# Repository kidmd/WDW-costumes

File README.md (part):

# Main Street Electrical Parade - Synchronized LED Costumes (WDW 10K)

This project powers synchronized, addressable LED lighting across **7 runner costumes** inspired by Disney's **Main Street Electrical Parade** for the Walt Disney World 10K.

Worn by our **7-member family running team** (2 brothers, 1 sister, 1 brother-in-law, and 3 sisters-in-law) and engineered with love by the **3 brothers** (2 running, 1 supporting behind the scenes).

---

## The Concept

Each runner wears a matte black technical running shirt outlined with glow-in-the-dark paint and illuminated by individually addressable **WS2812B "Seed" / Pebble LEDs** to replicate the vintage incandescent bulbs of the parade floats.

An **ESP32** microcontroller on each runner coordinates lighting patterns wirelessly in real time using **ESP-NOW** (connectionless peer-to-peer 2.4 GHz radio), requiring **no Wi-Fi router or cellular service**.

### The 7 Floats Roster

1. **The Train (Casey Jr.):** Warm white chugging locomotive headlight & steam pulses (parade leader pulling the Title Drum).
2. **The Title Drum:** Golden chasing marquee border, "Disney" electric text accent.
3. **The Turtle:** Whimsical spinning shell spirals, blinking amber eyes, and teal/green shell pattern.
4. **The Snail:** Multi-color rotating rainbow spiral shell wheels and neon antennae glow.
5. **The Pirate Ship:** Billowing crimson sails, antique gold masts & decks, and emerald ocean waves.
6. **Pete's Dragon (Elliott):** Chartreuse/green body scales with orange/red fire breathing effect.
7. **To Honor America (Flag & Eagle):** Patriotic red, white, and blue finale fireworks shimmer with majestic illuminated eagle.

---

## Hardware Specifications

* **Microcontrollers:** ESP32 (e.g. ESP32-WROOM-32D or Seeed XIAO ESP32)
* **LED Strands:** 200 WS2812B / WS2811 Addressable 5V Seed/Pebble Pixels (100 front + 100 back duplicated, black wire, ~1" to 2" spacing)
* **Data Resistor:** 220 Ω to 470 Ω inline on the data line between GPIO 16 and LED Data-In
* **Power Source:** 5V USB portable power bank (5,000–20,000 mAh rating, FastLED hardware limited to 2000 mA / 2.0A) per runner with built-in simulator Battery Life & Power Budget Calculator
* **Costume Simulation:** Visual browser-based layout engine (`python simulator.py` @ `localhost:8000`) with built-in presets (Pete's Dragon, The Pirate Ship, Casey Jr., Title Drum, Turtle, Snail, Eagle), multi-layer Cricut Heat Transfer Vinyl (HTV) cut file exporter suite (All-in-One master SVG, color-mat-by-color-mat SVGs, and 6×3mm tangent pill cutouts with 4-corner heat press registration marks), Universal Undo / Redo engine (`Ctrl+Z` / `Ctrl+Y`) with 50-step snapshot history and floating toolbar buttons, 7-Shirt Fleet Show Creator Studio featuring a 19-block choreography palette (traveling waves, dual collision shockwaves, butterfly ripples, fairy dust waterfalls, fleet pulses, wig-wags, sparkle storms, baton chases, and grand finales), interactive NLE-grade visual timeline block editor (drag-to-stretch, rolling trim, and drag-and-drop reordering), Animation Group Spatial Suite & Pre-Built Shape Stamp Library (parametric Circles/Wheels, Arches, Waves, Stars/Sparkles, Lines/Rulers, and Fireworks Starbursts with aspect-ratio correction, interactive click-to-place positioning, Cross-Shirt Clipboard, Rotate 90°, Flip H/V, Scale LED Spacing while maintaining exact shape, and auto-rearranging remaining unassigned LEDs), multi-float live Wi-Fi UDP streaming (`Opcode 0x02`), pre-race Corral Roll Call & ESP-NOW Fleet Radar (instant identification strobe, 4s rapid attendance wave, signal RSSI, battery voltage, and lineup readiness), race-day battery life calculator with 7-float power breakdown, double-tap 4-second rapid attendance wave, 300ms debounced one-shot trigger and early stop, "Snap to 30.0s" sequence normalization, JSON show persistence, 1-click & double-click Single View editing from fleet cards, real 700-LED mini-shirt visualizer, multi-mode wireless sync (ESP-NOW Wave, Free-Run, Show Sequence), full-graphic LED re-distribution (maintaining strictly 100 LEDs per shirt), and authentic runDisney 10K Race Bib (#1952) with Chip & Dale and BibBoards fastener clearance.
* **3D-Printable Flexible TPU Armor Plates & Protective Rear Lids (5-Color Multi-Material & Single STL):** High-speed parametric fabrication pipeline (`scripts/compile_clean_tpu_panel.py`) compiling wearable 9.0mm deep-chassis armor trays and matching **2.0mm protective rear cover lids** (`tpu_panel_{front|back}_lid.stl`). Features **5-Color Multi-Material FDM printing** (for Bambu Lab AMS / Snapmaker Dual) with a monolithic black structural chassis (`chassis_black.stl`), 4 zero-overlap jigsaw front color inlays, 3x3mm / Ø 3.4mm through-aperture windows for LEDs, and a **14-point M2 perimeter screw fastening system** (with dedicated extremity clamping at jaw, ears, tail tip, flank, and heel corners) with 1.2mm stepped alignment ridges. Includes 1-click **Bambu 3MF** and **5-Color ZIP bundles** (packaging tray, inlays, and rear lid), selectable plate sizing (Small ~6.5", Medium ~8.0", Large capped to $\le 245.0\text{ mm}$ for $256\times 256\text{ mm}$ build plates), selectable LED counts (50, 75, 100 LEDs), and an interactive 3D WebGL inspector (`#tpuPreviewModal` & `3d_panels/tpu_panel_preview.html`) with live Tray vs Rear Lid 3D inspection.
* **Universal 100mm × 100mm 6×6 LED Matrix Panels (Turnkey JLCPCB SMT & Felt Pocket):** Cost-optimized modular FR-4 PCB tile system. 4 identical 36-LED tiles cluster into a 144-LED chest array ($202\text{ mm} \times 202\text{ mm}$) featuring an authentic staggered brick layout with calibrated $17.0\text{ mm}$ pitch, making the 4-board cluster 100% optically seamless across the $2.0\text{ mm}$ felt living hinge gap. Available in two production variants:
  - **Front-Mounted Variant (`pcb/`):** 8 horizontal JST-PH 2.0mm ports set back $10.0\text{ mm}$ into inter-pixel valleys with diagonal $50\text{ mm}$ cable routing ($\le 5\text{ mm}$ height profile). Single-sided SMT using JLCPCB "Economic PCBA".
  - **Bottom-Mounted Variant (`pcb/bottom_connectors/`):** 100% flush front face (only 0.9mm LEDs and 0.5mm 0402 caps) for direct contact against fabric or 3D-printed faceplates with **0.0 mm gap and zero light bleed**. All 8 JST-PH headers are on the rear layer (`B.Cu`), featuring symmetrical **$22.0\text{ mm}$ straight-line spans** in all 4 directions for $50\text{ mm}$ pre-crimped JST cables. Requires JLCPCB double-sided "Standard PCBA" ($+\$0.80$ per board for a 75-board fleet order).
  - Both variants include 4× corner M3 screw holes, 4× dedicated fabric sewing eyelets, soldermask LED numbering (`1`..`36`), hidden component references for clean lenses, turnkey RS-274X Gerbers, JLCPCB BOM/CPL files, and interactive dual-view web inspectors (`universal_6x6_preview.html` and `universal_6x6_bottom_preview.html`).
* **Monolithic 200mm × 200mm LED Panels (Zero-Wire Single-Sided SMT Displays):** Large single-piece $200.0\text{ mm} \times 200.0\text{ mm}$ ($7.87'' \times 7.87''$) boards featuring 100% internal etched copper wiring (zero inter-tile jumper cables) and pure single-sided SMT assembly (LEDs and Caps on Top layer only, qualifying for JLCPCB **Economic PCBA** at $\sim \$15.00$ setup fee, saving $\$55.00$ per batch). Equipped with $2.54\text{ mm}$ pitch plated through-hole solder pins for IN and OUT (solderable from Front or Back) and dual S-curve wire strain-relief anchor holes. Available in two density options:
  - **144-LED Model (`pcb/monolithic_200mm_144/`):** 12×12 staggered brick matrix ($15.5\text{ mm} \times 16.0\text{ mm}$ pitch). Complete with RS-274X Gerbers, BOM, CPL, KiCad PCB, and interactive HTML preview. Fleet cost for 8 suits (18 boards): **$\approx \$220.72$ ($\$27.59$ per runner for Front + Back)**.
  - **288-LED Double-Density Model (`pcb/monolithic_200mm_288/`):** Exactly twice as many LEDs ($144 \times 2 = 288$ LEDs) in an 18×16 isotropic offset lattice ($11.6\text{ mm} \times 10.6\text{ mm}$ pitch). High-definition "Retina" resolution for intricate parade graphics. FastLED hardware power limited to 2.0A. Complete with RS-274X Gerbers, BOM, CPL, KiCad PCB, and interactive HTML preview. Fleet cost for 8 suits (18 boards): **$\approx \$368.45$ ($\$46.06$ per runner for Front + Back)**.
* **3D-Printable PLA PCB Test Mockups (`3d_panels/mockups/`):** Physics-calibrated physical test "mules" to evaluate chest curvature, thickness, weight, and bounce on a running shirt before ordering from JLCPCB. Using the **2.5mm Equivalence Rule**, printing at 100% solid infill matches both the real $2.5\text{ mm}$ board+LED envelope AND the exact weight (**$123.7\text{ grams}$ PLA vs. $126.5\text{ grams}$ real PCB — a 97.8% match!**). Includes `mockup_monolithic_200x200.stl`, `mockup_modular_100x100.stl`, and an interactive 3D WebGL preview (`mockups_preview.html`).
* **Pete's Dragon 200mm × 200mm Optical Backlighting Test Panels (`3d_panels/backlight_test/`):** Flat multi-color test panels designed to evaluate filament translucency and rear LED backlighting diffusion across 4 calibrated thicknesses (**1.00 mm, 0.80 mm, 0.60 mm, and 0.48 mm**). Features a pure flat $200.0\text{ mm} \times 200.0\text{ mm}$ black chassis (all LED holes, trenches, walls, eyelets, and screw holes removed), with Pete's Dragon ($180.0\text{ mm} \times 163.2\text{ mm}$) centered inside a $180\text{ mm}$ square. All artwork colors (Green, Magenta, Yellow, White) extend 100% through the full Z thickness for optical transmission. Includes native multi-material `.3mf` files (Bambu Studio / OrcaSlicer / Snapmaker Luban), individual color STLs, parametric OpenSCAD script, and an interactive 3D WebGL preview (`backlight_test_preview.html`).
* **BTF-LIGHTING 16×16 (256-Pixel) Flexible FPCB Matrix (Default Standard Architecture):** The primary costume standard across the simulator and firmware. Features a commercial $160.0\text{ mm} \times 160.0\text{ mm}$ ($10.0\text{ mm}$ pitch) WS2812B ECO 256-LED flexible matrix mounted behind a **$176.0\text{ mm} \times 176.0\text{ mm}$ flat square 3D-printed plate** ($2.0\text{ mm}$ perimeter frame, full $2.0\text{ mm}$ pocket depth with strictly $0.0\text{ mm}$ lip, soft 6.0mm anti-snag rounded corners, and 4 corner $\varnothing 2.8\text{ mm}$ shirt-stitching holes). Evenly distributes **~50 Windowed LEDs** ($5.4\text{ mm} \times 5.4\text{ mm}$ through-hole apertures) and **~25 Backlighting LEDs** (diffused subsurface glow through thin colored PLA/TPU at 50% brightness) via Farthest-Point Sampling while keeping the remaining **~181 LEDs Dark** (~1.35A max draw @ 5V). Features a **$0.40\text{ mm}$ Clear Diffuser Backing Layer** default (spanning the full $160.4 \times 160.4\text{ mm}$ cavity flush to the 2mm frame), default **$0.60\text{ mm}$ Front Graphic Faceplate** ($1.00\text{ mm}$ total panel thickness), **$2.00\text{ mm}$ Perimeter Frame Depth**, face-down print orientation on PEI bed, automatic slicer pause at $Z = 0.60\text{ mm}$ (Layer 4) for swapping Nozzle 3 / Toolhead 3 on the Snapmaker U1 to Clear filament, and native multi-material `.3mf` project with embedded extruder mapping. Governed by a **Global Hardware Architecture Switcher** (`[ 🔲 16×16 Matrix (Default) ]` | `[ 🧵 Fairy Lights (Legacy) ]`) in the top navigation bar, decluttering the Layout and Deploy tabs (top-header **📁 Upload Artwork** modal, legacy-scoped placement guides, fixed 57% height/100% scale race bib, and Groups-tab-dedicated inspector) while preserving 100% backward compatibility for legacy prototype fairy light rigs.

---

## Wireless Synchronization (ESP-NOW)

* **Protocol:** ESP-NOW broadcast (Destination MAC `FF:FF:FF:FF:FF:FF`).
* **Architecture:**
  * **Float 1 (Primary Master Leader):** Front locomotive broadcasting timing ticks, BPM tempo, master brightness, show triggers, and photo mode.
  * **Float 7 (Co-Leader / Rear Marshal):** Rear anchor with full co-leader authority to command the rear pack independently if runners split.
  * **Floats 2–6 (Followers):** Listen to broadcast packets, lock to master clock, and execute individual autonomous sequences or synchronized routines.
* **Dual Hardware Button Controls (Button 1: GPIO 4 / BOOT GPIO 0, Button 2: GPIO 33):**
  * **Power-Up (Plug USB):** Boots directly into **🌙 Corral Standby Mode** (12% dim midnight starlight twinkle, < 120mA), saving 80%+ battery during the 60–90 min starting wait.
  * **Button 1 — Single Tap (< 600ms):**
    * 👑 *Leader (Float 1 & 7):* When asleep or in Photo Mode, wakes **ENTIRE FLEET** into **Solo Show Mode** (individual float identities). When running awake, launches the **30s Synchronized Fleet Routine** (or toggles/cancels during active routine).
    * 👥 *Follower (Floats 2–6):* When asleep or in Photo Mode, wakes/exits **THAT RUNNER ONLY** into Solo Show Mode. When running awake, **IGNORED** (keeps parade show running without accidental interruption).
  * **Button 1 — Double Tap (< 400ms):**
    * 👑 *Leader:* Triggers **⚡ 4-Second Rapid Attendance Roll Call** wave across all 7 costumes.
    * 👥 *Follower:* Ignored (roll call reserved for Leader).
  * **Button 1 — Long Hold (5s):**
    * Enter **Float ID Configuration Mode** (1 to 7) with a 1s–4s progressive white LED charging meter and permanent NVS flash auto-save. Releasing before 5s cleanly aborts back to baseline without triggering show routines.
  * **Button 2 — Single Tap (< 600ms):**
    * 👑 *Leader:* Toggles **📸 Castle Photo Mode** (solid, steady, non-flickering full graphic background colors) across the **ENTIRE FLEET**.
    * 👥 *Follower:* Toggles **📸 Castle Photo Mode** **LOCALLY** (solid full graphic background colors) for that runner.
  * **Button 2 — Double Tap (< 400ms):**
    * 👑 *Leader:* Toggles **✨ 3% Warm White Starlight Mode** (~2500K golden incandescent filament glow with pure diamond sparkles) across the **ENTIRE FLEET** (with 2-pulse warm white confirmation). Tap or double-tap again resumes parade show.
    * 👥 *Follower:* Toggles **✨ 3% Warm White Starlight Mode** **LOCALLY** for that runner.
  * **Button 2 — Long Hold (3s):**
    * 👑 *Leader:* Drops **ENTIRE FLEET into Corral Standby (Sleep) Mode**. Stays locked in Standby even if held >3s—requiring an explicit click to enter Photo Mode.
    * 👥 *Follower:* Drops **THAT RUNNER ONLY into Corral Standby Mode**. Stays locked in Standby even if held >3s—waiting for physical release so it never accidentally pops into Photo Mode.

---

## ⚡ Quick Start for Family Runners & Crew (No Git Required!)

You don't need Git, Google Antigravity, or any programming tools:
1. **Download:** Click the green **`<> Code`** button above ➔ **`Download ZIP`** (or [Click Here to Download ZIP](https://github.com/kidmd/WDW-costumes/archive/refs/heads/main.zip)).
2. **Extract:** Right-click the `.zip` file and select **Extract All...** to any folder on your computer.
3. **Plug in & Flash:** Connect your ESP32 via USB and double-click **`flash_firmware.bat`** (Windows) or **`flash_firmware.command`** (Mac).
4. See **[`FLASHING_INSTRUCTIONS.md`](FLASHING_INSTRUCTIONS.md)** for complete hardware wiring and float selection instructions.

---

## Project Structure & Documentation

* [`ESP32_WIRING_PLAN.md`](ESP32_WIRING_PLAN.md): **🔌 ESP32 Hardware Wiring Plan & Electrical Specification** — Complete schematics, pinout tables, tactile button wiring, 4-pin orientation guide, 220–470 Ω data resistor, power bus injection, and computer power isolation rules.
* [`RACE_DAY_BUTTON_GUIDE.md`](RACE_DAY_BUTTON_GUIDE.md): **🏃🏰 Race Day Button Field Guide & Controller Cheat Sheet** — Pocket manual with gesture timings, Leader vs Follower matrices, chronological corral countdown playbook, and state flow diagrams.
* [`RACE_DAY_PACKING_CHECKLIST.md`](RACE_DAY_PACKING_CHECKLIST.md): **🏰 Race Day Packing Checklist & Field Manual** — Pre-race hardware checklist, spare ESP32s, battery survival, repair toolkit, weather kit, and countdown timeline for the 7-runner family team.
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
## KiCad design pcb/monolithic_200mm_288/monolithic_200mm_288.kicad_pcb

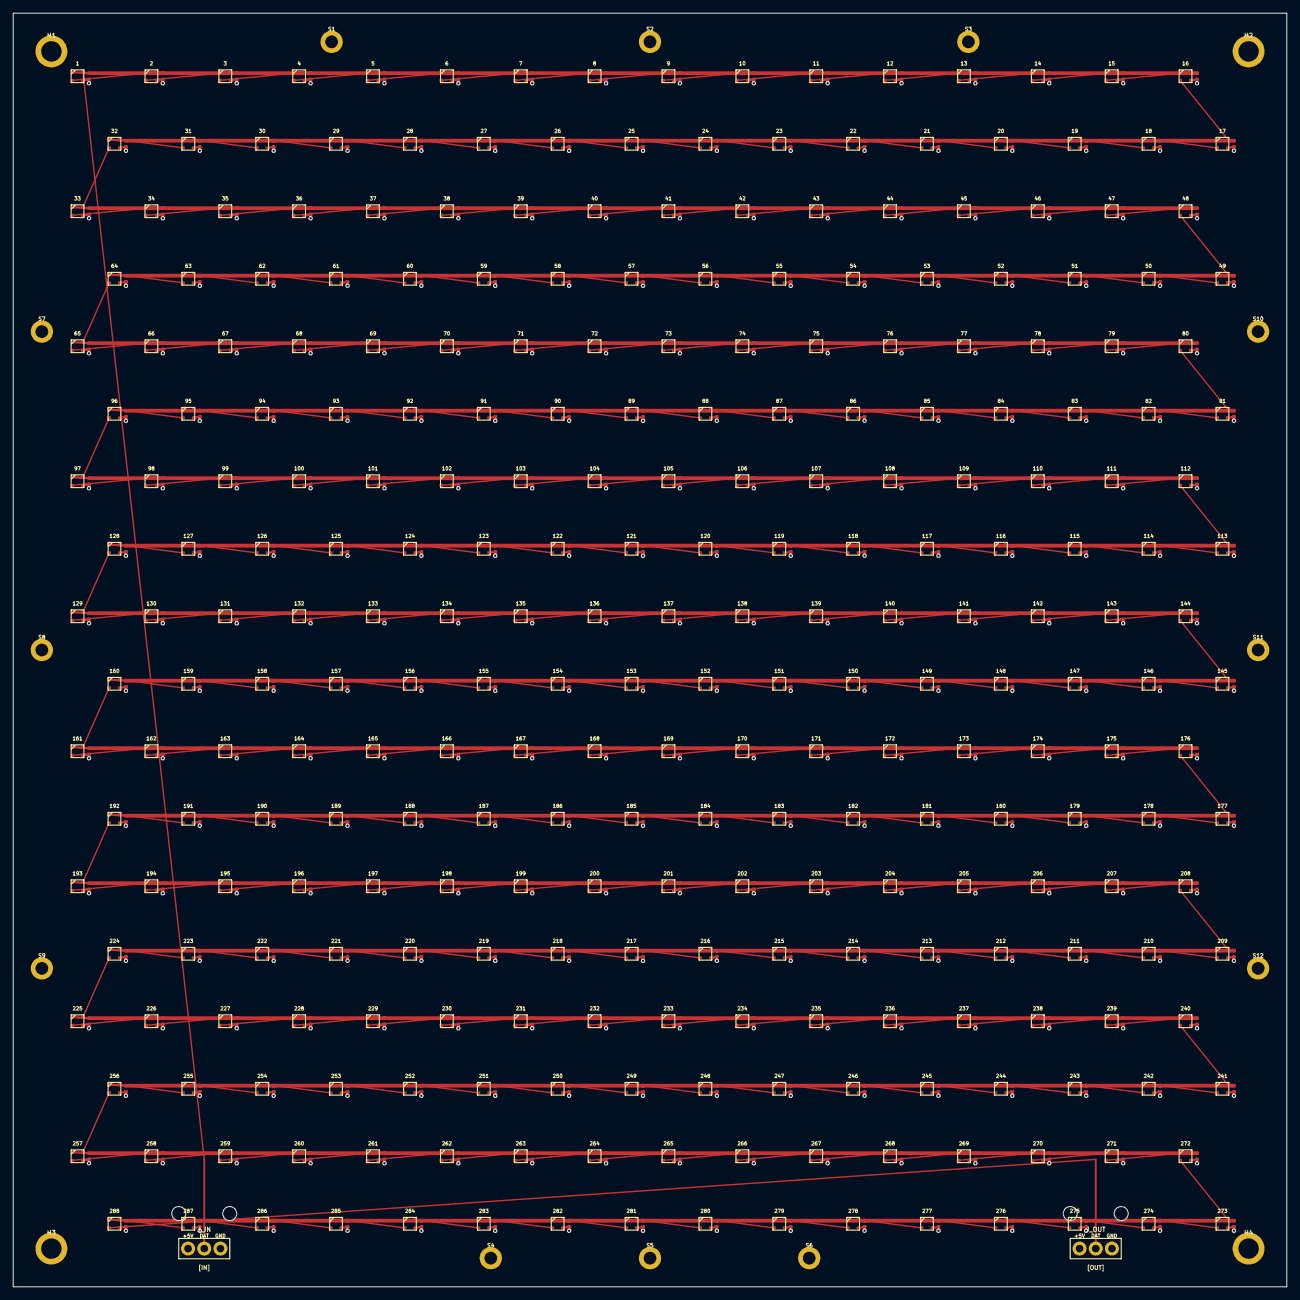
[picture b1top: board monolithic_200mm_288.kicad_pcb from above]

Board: 2 copper layers, 200.0 x 200.0 mm, 594 parts (0 on the bottom side), 291 nets.

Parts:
C1, C2, C3, C4, C5, C6, C7, C8, C9, C10, C11, C12, C13, C14, C15, C16, C17, C18, C19, C20, C21, C22, C23, C24, C25, C26, C27, C28, C29, C30, C31, C32, C33, C34, C35, C36, C37, C38, C39, C40, C41, C42, C43, C44, C45, C46, C47, C48, C49, C50, C51, C52, C53, C54, C55, C56, C57, C58, C59, C60, C61, C62, C63, C64, C65, C66, C67, C68, C69, C70, C71, C72, C73, C74, C75, C76, C77, C78, C79, C80, C81, C82, C83, C84, C85, C86, C87, C88, C89, C90, C91, C92, C93, C94, C95, C96, C97, C98, C99, C100, C101, C102, C103, C104, C105, C106, C107, C108, C109, C110, C111, C112, C113, C114, C115, C116, C117, C118, C119, C120, C121, C122, C123, C124, C125, C126, C127, C128, C129, C130, C131, C132, C133, C134, C135, C136, C137, C138, C139, C140, C141, C142, C143, C144, C145, C146, C147, C148, C149, C150, C151, C152, C153, C154, C155, C156, C157, C158, C159, C160, C161, C162, C163, C164, C165, C166, C167, C168, C169, C170, C171, C172, C173, C174, C175, C176, C177, C178, C179, C180, C181, C182, C183, C184, C185, C186, C187, C188, C189, C190, C191, C192, C193, C194, C195, C196, C197, C198, C199, C200, C201, C202, C203, C204, C205, C206, C207, C208, C209, C210, C211, C212, C213, C214, C215, C216, C217, C218, C219, C220, C221, C222, C223, C224, C225, C226, C227, C228, C229, C230, C231, C232, C233, C234, C235, C236, C237, C238, C239, C240, C241, C242, C243, C244, C245, C246, C247, C248, C249, C250, C251, C252, C253, C254, C255, C256, C257, C258, C259, C260, C261, C262, C263, C264, C265, C266, C267, C268, C269, C270, C271, C272, C273, C274, C275, C276, C277, C278, C279, C280, C281, C282, C283, C284, C285, C286, C287, C288: C_0402_1005Metric
D1, D2, D3, D4, D5, D6, D7, D8, D9, D10, D11, D12, D13, D14, D15, D16, D17, D18, D19, D20, D21, D22, D23, D24, D25, D26, D27, D28, D29, D30, D31, D32, D33, D34, D35, D36, D37, D38, D39, D40, D41, D42, D43, D44, D45, D46, D47, D48, D49, D50, D51, D52, D53, D54, D55, D56, D57, D58, D59, D60, D61, D62, D63, D64, D65, D66, D67, D68, D69, D70, D71, D72, D73, D74, D75, D76, D77, D78, D79, D80, D81, D82, D83, D84, D85, D86, D87, D88, D89, D90, D91, D92, D93, D94, D95, D96, D97, D98, D99, D100, D101, D102, D103, D104, D105, D106, D107, D108, D109, D110, D111, D112, D113, D114, D115, D116, D117, D118, D119, D120, D121, D122, D123, D124, D125, D126, D127, D128, D129, D130, D131, D132, D133, D134, D135, D136, D137, D138, D139, D140, D141, D142, D143, D144, D145, D146, D147, D148, D149, D150, D151, D152, D153, D154, D155, D156, D157, D158, D159, D160, D161, D162, D163, D164, D165, D166, D167, D168, D169, D170, D171, D172, D173, D174, D175, D176, D177, D178, D179, D180, D181, D182, D183, D184, D185, D186, D187, D188, D189, D190, D191, D192, D193, D194, D195, D196, D197, D198, D199, D200, D201, D202, D203, D204, D205, D206, D207, D208, D209, D210, D211, D212, D213, D214, D215, D216, D217, D218, D219, D220, D221, D222, D223, D224, D225, D226, D227, D228, D229, D230, D231, D232, D233, D234, D235, D236, D237, D238, D239, D240, D241, D242, D243, D244, D245, D246, D247, D248, D249, D250, D251, D252, D253, D254, D255, D256, D257, D258, D259, D260, D261, D262, D263, D264, D265, D266, D267, D268, D269, D270, D271, D272, D273, D274, D275, D276, D277, D278, D279, D280, D281, D282, D283, D284, D285, D286, D287, D288: LED_WS2812B-2020_PLCC4_2.0x2.0mm
H1, H2, H3, H4: MountingHole_3.2mm_M3
J_IN: PinHeader_1x03_P2.54mm_Vertical
J_OUT: PinHeader_1x03_P2.54mm_Vertical
S1, S2, S3, S4, S5, S6, S7, S8, S9, S10, S11, S12: MountingHole_2.0mm

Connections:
+5V: C1.1, C2.1, C3.1, C4.1, C5.1, C6.1, C7.1, C8.1, C9.1, C10.1, C11.1, C12.1, C13.1, C14.1, C15.1, C16.1, C17.1, C18.1, C19.1, C20.1, C21.1, C22.1, C23.1, C24.1, C25.1, C26.1, C27.1, C28.1, C29.1, C30.1, C31.1, C32.1, C33.1, C34.1, C35.1, C36.1, C37.1, C38.1, C39.1, C40.1, C41.1, C42.1, C43.1, C44.1, C45.1, C46.1, C47.1, C48.1, C49.1, C50.1, C51.1, C52.1, C53.1, C54.1, C55.1, C56.1, C57.1, C58.1, C59.1, C60.1, C61.1, C62.1, C63.1, C64.1, C65.1, C66.1, C67.1, C68.1, C69.1, C70.1, C71.1, C72.1, C73.1, C74.1, C75.1, C76.1, C77.1, C78.1, C79.1, C80.1, C81.1, C82.1, C83.1, C84.1, C85.1, C86.1, C87.1, C88.1, C89.1, C90.1, C91.1, C92.1, C93.1, C94.1, C95.1, C96.1, C97.1, C98.1, C99.1, C100.1, C101.1, C102.1, C103.1, C104.1, C105.1, C106.1, C107.1, C108.1, C109.1, C110.1, C111.1, C112.1, C113.1, C114.1, C115.1, C116.1, C117.1, C118.1, C119.1, C120.1, C121.1, C122.1, C123.1, C124.1, C125.1, C126.1, C127.1, C128.1, C129.1, C130.1, C131.1, C132.1, C133.1, C134.1, C135.1, C136.1, C137.1, C138.1, C139.1, C140.1, C141.1, C142.1, C143.1, C144.1, C145.1, C146.1, C147.1, C148.1, C149.1, C150.1, C151.1, C152.1, C153.1, C154.1, C155.1, C156.1, C157.1, C158.1, C159.1, C160.1, C161.1, C162.1, C163.1, C164.1, C165.1, C166.1, C167.1, C168.1, C169.1, C170.1, C171.1, C172.1, C173.1, C174.1, C175.1, C176.1, C177.1, C178.1, C179.1, C180.1, C181.1, C182.1, C183.1, C184.1, C185.1, C186.1, C187.1, C188.1, C189.1, C190.1, C191.1, C192.1, C193.1, C194.1, C195.1, C196.1, C197.1, C198.1, C199.1, C200.1, C201.1, C202.1, C203.1, C204.1, C205.1, C206.1, C207.1, C208.1, C209.1, C210.1, C211.1, C212.1, C213.1, C214.1, C215.1, C216.1, C217.1, C218.1, C219.1, C220.1, C221.1, C222.1, C223.1, C224.1, C225.1, C226.1, C227.1, C228.1, C229.1, C230.1, C231.1, C232.1, C233.1, C234.1, C235.1, C236.1, C237.1, C238.1, C239.1, C240.1, C241.1, C242.1, C243.1, C244.1, C245.1, C246.1, C247.1, C248.1, C249.1, C250.1, C251.1, C252.1, C253.1, C254.1, C255.1, C256.1, C257.1, C258.1, C259.1, C260.1, C261.1, C262.1, C263.1, C264.1, C265.1, C266.1, C267.1, C268.1, C269.1, C270.1, C271.1, C272.1, C273.1, C274.1, C275.1, C276.1, C277.1, C278.1, C279.1, C280.1, C281.1, C282.1, C283.1, C284.1, C285.1, C286.1, C287.1, C288.1, D1.1, D2.1, D3.1, D4.1, D5.1, D6.1, D7.1, D8.1, D9.1, D10.1, D11.1, D12.1, D13.1, D14.1, D15.1, D16.1, D17.1, D18.1, D19.1, D20.1, D21.1, D22.1, D23.1, D24.1, D25.1, D26.1, D27.1, D28.1, D29.1, D30.1, D31.1, D32.1, D33.1, D34.1, D35.1, D36.1, D37.1, D38.1, D39.1, D40.1, D41.1, D42.1, D43.1, D44.1, D45.1, D46.1, D47.1, D48.1, D49.1, D50.1, D51.1, D52.1, D53.1, D54.1, D55.1, D56.1, D57.1, D58.1, D59.1, D60.1, D61.1, D62.1, D63.1, D64.1, D65.1, D66.1, D67.1, D68.1, D69.1, D70.1, D71.1, D72.1, D73.1, D74.1, D75.1, D76.1, D77.1, D78.1, D79.1, D80.1, D81.1, D82.1, D83.1, D84.1, D85.1, D86.1, D87.1, D88.1, D89.1, D90.1, D91.1, D92.1, D93.1, D94.1, D95.1, D96.1, D97.1, D98.1, D99.1, D100.1, D101.1, D102.1, D103.1, D104.1, D105.1, D106.1, D107.1, D108.1, D109.1, D110.1, D111.1, D112.1, D113.1, D114.1, D115.1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
DATA_1: D1.4, J_IN.2
DATA_2: D1.2, D2.4
DATA_3: D2.2, D3.4
DATA_4: D3.2, D4.4
DATA_5: D4.2, D5.4
DATA_6: D5.2, D6.4
DATA_7: D6.2, D7.4
DATA_8: D7.2, D8.4
DATA_9: D8.2, D9.4
DATA_10: D9.2, D10.4
DATA_11: D10.2, D11.4
DATA_12: D11.2, D12.4
DATA_13: D12.2, D13.4
DATA_14: D13.2, D14.4
DATA_15: D14.2, D15.4
DATA_16: D15.2, D16.4
DATA_17: D16.2, D17.4
DATA_18: D17.2, D18.4
DATA_19: D18.2, D19.4
DATA_20: D19.2, D20.4
DATA_21: D20.2, D21.4
DATA_22: D21.2, D22.4
DATA_23: D22.2, D23.4
DATA_24: D23.2, D24.4
DATA_25: D24.2, D25.4
DATA_26: D25.2, D26.4
DATA_27: D26.2, D27.4
DATA_28: D27.2, D28.4
DATA_29: D28.2, D29.4
DATA_30: D29.2, D30.4
DATA_31: D30.2, D31.4
DATA_32: D31.2, D32.4
DATA_33: D32.2, D33.4
DATA_34: D33.2, D34.4
DATA_35: D34.2, D35.4
DATA_36: D35.2, D36.4
DATA_37: D36.2, D37.4
DATA_38: D37.2, D38.4
DATA_39: D38.2, D39.4
DATA_40: D39.2, D40.4
DATA_41: D40.2, D41.4
DATA_42: D41.2, D42.4
DATA_43: D42.2, D43.4
DATA_44: D43.2, D44.4
DATA_45: D44.2, D45.4
DATA_46: D45.2, D46.4
DATA_47: D46.2, D47.4
DATA_48: D47.2, D48.4
DATA_49: D48.2, D49.4
DATA_50: D49.2, D50.4
DATA_51: D50.2, D51.4
DATA_52: D51.2, D52.4
DATA_53: D52.2, D53.4
DATA_54: D53.2, D54.4
DATA_55: D54.2, D55.4
DATA_56: D55.2, D56.4
DATA_57: D56.2, D57.4
DATA_58: D57.2, D58.4
DATA_59: D58.2, D59.4
DATA_60: D59.2, D60.4
DATA_61: D60.2, D61.4
DATA_62: D61.2, D62.4
DATA_63: D62.2, D63.4
DATA_64: D63.2, D64.4
DATA_65: D64.2, D65.4
DATA_66: D65.2, D66.4
DATA_67: D66.2, D67.4
DATA_68: D67.2, D68.4
DATA_69: D68.2, D69.4
DATA_70: D69.2, D70.4
DATA_71: D70.2, D71.4
DATA_72: D71.2, D72.4
DATA_73: D72.2, D73.4
DATA_74: D73.2, D74.4
DATA_75: D74.2, D75.4
DATA_76: D75.2, D76.4
DATA_77: D76.2, D77.4
DATA_78: D77.2, D78.4
DATA_79: D78.2, D79.4
DATA_80: D79.2, D80.4
DATA_81: D80.2, D81.4
DATA_82: D81.2, D82.4
DATA_83: D82.2, D83.4
DATA_84: D83.2, D84.4
DATA_85: D84.2, D85.4
DATA_86: D85.2, D86.4
DATA_87: D86.2, D87.4
DATA_88: D87.2, D88.4
DATA_89: D88.2, D89.4
DATA_90: D89.2, D90.4
DATA_91: D90.2, D91.4
DATA_92: D91.2, D92.4
DATA_93: D92.2, D93.4
DATA_94: D93.2, D94.4
DATA_95: D94.2, D95.4
DATA_96: D95.2, D96.4
DATA_97: D96.2, D97.4
DATA_98: D97.2, D98.4
DATA_99: D98.2, D99.4
DATA_100: D99.2, D100.4
DATA_101: D100.2, D101.4
DATA_102: D101.2, D102.4
DATA_103: D102.2, D103.4
DATA_104: D103.2, D104.4
DATA_105: D104.2, D105.4
DATA_106: D105.2, D106.4
DATA_107: D106.2, D107.4
DATA_108: D107.2, D108.4
DATA_109: D108.2, D109.4
DATA_110: D109.2, D110.4
DATA_111: D110.2, D111.4
DATA_112: D111.2, D112.4
DATA_113: D112.2, D113.4
DATA_114: D113.2, D114.4
DATA_115: D114.2, D115.4
DATA_116: D115.2, D116.4
DATA_117: D116.2, D117.4
DATA_118: D117.2, D118.4
DATA_119: D118.2, D119.4
DATA_120: D119.2, D120.4
DATA_121: D120.2, D121.4
DATA_122: D121.2, D122.4
DATA_123: D122.2, D123.4
DATA_124: D123.2, D124.4
DATA_125: D124.2, D125.4
DATA_126: D125.2, D126.4
DATA_127: D126.2, D127.4
DATA_128: D127.2, D128.4
DATA_129: D128.2, D129.4
DATA_130: D129.2, D130.4
DATA_131: D130.2, D131.4
DATA_132: D131.2, D132.4
DATA_133: D132.2, D133.4
DATA_134: D133.2, D134.4
DATA_135: D134.2, D135.4
DATA_136: D135.2, D136.4
DATA_137: D136.2, D137.4
DATA_138: D137.2, D138.4
DATA_139: D138.2, D139.4
DATA_140: D139.2, D140.4
DATA_141: D140.2, D141.4
DATA_142: D141.2, D142.4
DATA_143: D142.2, D143.4
DATA_144: D143.2, D144.4
DATA_145: D144.2, D145.4
DATA_146: D145.2, D146.4
DATA_147: D146.2, D147.4
DATA_148: D147.2, D148.4
DATA_149: D148.2, D149.4
DATA_150: D149.2, D150.4
DATA_151: D150.2, D151.4
DATA_152: D151.2, D152.4
DATA_153: D152.2, D153.4
DATA_154: D153.2, D154.4
DATA_155: D154.2, D155.4
DATA_156: D155.2, D156.4
DATA_157: D156.2, D157.4
DATA_158: D157.2, D158.4
DATA_159: D158.2, D159.4
DATA_160: D159.2, D160.4
DATA_161: D160.2, D161.4
DATA_162: D161.2, D162.4
DATA_163: D162.2, D163.4
DATA_164: D163.2, D164.4
DATA_165: D164.2, D165.4
DATA_166: D165.2, D166.4
DATA_167: D166.2, D167.4
DATA_168: D167.2, D168.4
DATA_169: D168.2, D169.4
DATA_170: D169.2, D170.4
DATA_171: D170.2, D171.4
DATA_172: D171.2, D172.4
DATA_173: D172.2, D173.4
DATA_174: D173.2, D174.4
DATA_175: D174.2, D175.4
DATA_176: D175.2, D176.4
DATA_177: D176.2, D177.4
DATA_178: D177.2, D178.4
DATA_179: D178.2, D179.4
DATA_180: D179.2, D180.4
DATA_181: D180.2, D181.4
DATA_182: D181.2, D182.4
DATA_183: D182.2, D183.4
DATA_184: D183.2, D184.4
DATA_185: D184.2, D185.4
DATA_186: D185.2, D186.4
DATA_187: D186.2, D187.4
DATA_188: D187.2, D188.4
DATA_189: D188.2, D189.4
DATA_190: D189.2, D190.4
DATA_191: D190.2, D191.4
DATA_192: D191.2, D192.4
DATA_193: D192.2, D193.4
DATA_194: D193.2, D194.4
DATA_195: D194.2, D195.4
DATA_196: D195.2, D196.4
DATA_197: D196.2, D197.4
DATA_198: D197.2, D198.4
DATA_199: D198.2, D199.4
DATA_200: D199.2, D200.4
DATA_201: D200.2, D201.4
DATA_202: D201.2, D202.4
DATA_203: D202.2, D203.4
DATA_204: D203.2, D204.4
DATA_205: D204.2, D205.4
DATA_206: D205.2, D206.4
DATA_207: D206.2, D207.4
DATA_208: D207.2, D208.4
DATA_209: D208.2, D209.4
DATA_210: D209.2, D210.4
DATA_211: D210.2, D211.4
DATA_212: D211.2, D212.4
DATA_213: D212.2, D213.4
DATA_214: D213.2, D214.4
DATA_215: D214.2, D215.4
DATA_216: D215.2, D216.4
DATA_217: D216.2, D217.4
DATA_218: D217.2, D218.4
DATA_219: D218.2, D219.4
DATA_220: D219.2, D220.4
DATA_221: D220.2, D221.4
DATA_222: D221.2, D222.4
DATA_223: D222.2, D223.4
DATA_224: D223.2, D224.4
DATA_225: D224.2, D225.4
DATA_226: D225.2, D226.4
DATA_227: D226.2, D227.4
DATA_228: D227.2, D228.4
DATA_229: D228.2, D229.4
DATA_230: D229.2, D230.4
DATA_231: D230.2, D231.4
DATA_232: D231.2, D232.4
DATA_233: D232.2, D233.4
DATA_234: D233.2, D234.4
DATA_235: D234.2, D235.4
DATA_236: D235.2, D236.4
DATA_237: D236.2, D237.4
DATA_238: D237.2, D238.4
DATA_239: D238.2, D239.4
DATA_240: D239.2, D240.4
DATA_241: D240.2, D241.4
DATA_242: D241.2, D242.4
DATA_243: D242.2, D243.4
DATA_244: D243.2, D244.4
DATA_245: D244.2, D245.4
DATA_246: D245.2, D246.4
DATA_247: D246.2, D247.4
DATA_248: D247.2, D248.4
DATA_249: D248.2, D249.4
DATA_250: D249.2, D250.4
DATA_251: D250.2, D251.4
DATA_252: D251.2, D252.4
DATA_253: D252.2, D253.4
DATA_254: D253.2, D254.4
DATA_255: D254.2, D255.4
DATA_256: D255.2, D256.4
DATA_257: D256.2, D257.4
DATA_258: D257.2, D258.4
DATA_259: D258.2, D259.4
DATA_260: D259.2, D260.4
DATA_261: D260.2, D261.4
DATA_262: D261.2, D262.4
DATA_263: D262.2, D263.4
DATA_264: D263.2, D264.4
DATA_265: D264.2, D265.4
DATA_266: D265.2, D266.4
DATA_267: D266.2, D267.4
DATA_268: D267.2, D268.4
DATA_269: D268.2, D269.4
DATA_270: D269.2, D270.4
DATA_271: D270.2, D271.4
DATA_272: D271.2, D272.4
DATA_273: D272.2, D273.4
DATA_274: D273.2, D274.4
DATA_275: D274.2, D275.4
DATA_276: D275.2, D276.4
DATA_277: D276.2, D277.4
DATA_278: D277.2, D278.4
DATA_279: D278.2, D279.4
DATA_280: D279.2, D280.4
DATA_281: D280.2, D281.4
DATA_282: D281.2, D282.4
DATA_283: D282.2, D283.4
DATA_284: D283.2, D284.4
DATA_285: D284.2, D285.4
DATA_286: D285.2, D286.4
DATA_287: D286.2, D287.4
DATA_288: D287.2, D288.4
DATA_289: D288.2, J_OUT.2
GND: C1.2, C2.2, C3.2, C4.2, C5.2, C6.2, C7.2, C8.2, C9.2, C10.2, C11.2, C12.2, C13.2, C14.2, C15.2, C16.2, C17.2, C18.2, C19.2, C20.2, C21.2, C22.2, C23.2, C24.2, C25.2, C26.2, C27.2, C28.2, C29.2, C30.2, C31.2, C32.2, C33.2, C34.2, C35.2, C36.2, C37.2, C38.2, C39.2, C40.2, C41.2, C42.2, C43.2, C44.2, C45.2, C46.2, C47.2, C48.2, C49.2, C50.2, C51.2, C52.2, C53.2, C54.2, C55.2, C56.2, C57.2, C58.2, C59.2, C60.2, C61.2, C62.2, C63.2, C64.2, C65.2, C66.2, C67.2, C68.2, C69.2, C70.2, C71.2, C72.2, C73.2, C74.2, C75.2, C76.2, C77.2, C78.2, C79.2, C80.2, C81.2, C82.2, C83.2, C84.2, C85.2, C86.2, C87.2, C88.2, C89.2, C90.2, C91.2, C92.2, C93.2, C94.2, C95.2, C96.2, C97.2, C98.2, C99.2, C100.2, C101.2, C102.2, C103.2, C104.2, C105.2, C106.2, C107.2, C108.2, C109.2, C110.2, C111.2, C112.2, C113.2, C114.2, C115.2, C116.2, C117.2, C118.2, C119.2, C120.2, C121.2, C122.2, C123.2, C124.2, C125.2, C126.2, C127.2, C128.2, C129.2, C130.2, C131.2, C132.2, C133.2, C134.2, C135.2, C136.2, C137.2, C138.2, C139.2, C140.2, C141.2, C142.2, C143.2, C144.2, C145.2, C146.2, C147.2, C148.2, C149.2, C150.2, C151.2, C152.2, C153.2, C154.2, C155.2, C156.2, C157.2, C158.2, C159.2, C160.2, C161.2, C162.2, C163.2, C164.2, C165.2, C166.2, C167.2, C168.2, C169.2, C170.2, C171.2, C172.2, C173.2, C174.2, C175.2, C176.2, C177.2, C178.2, C179.2, C180.2, C181.2, C182.2, C183.2, C184.2, C185.2, C186.2, C187.2, C188.2, C189.2, C190.2, C191.2, C192.2, C193.2, C194.2, C195.2, C196.2, C197.2, C198.2, C199.2, C200.2, C201.2, C202.2, C203.2, C204.2, C205.2, C206.2, C207.2, C208.2, C209.2, C210.2, C211.2, C212.2, C213.2, C214.2, C215.2, C216.2, C217.2, C218.2, C219.2, C220.2, C221.2, C222.2, C223.2, C224.2, C225.2, C226.2, C227.2, C228.2, C229.2, C230.2, C231.2, C232.2, C233.2, C234.2, C235.2, C236.2, C237.2, C238.2, C239.2, C240.2, C241.2, C242.2, C243.2, C244.2, C245.2, C246.2, C247.2, C248.2, C249.2, C250.2, C251.2, C252.2, C253.2, C254.2, C255.2, C256.2, C257.2, C258.2, C259.2, C260.2, C261.2, C262.2, C263.2, C264.2, C265.2, C266.2, C267.2, C268.2, C269.2, C270.2, C271.2, C272.2, C273.2, C274.2, C275.2, C276.2, C277.2, C278.2, C279.2, C280.2, C281.2, C282.2, C283.2, C284.2, C285.2, C286.2, C287.2, C288.2, D1.3, D2.3, D3.3, D4.3, D5.3, D6.3, D7.3, D8.3, D9.3, D10.3, D11.3, D12.3, D13.3, D14.3, D15.3, D16.3, D17.3, D18.3, D19.3, D20.3, D21.3, D22.3, D23.3, D24.3, D25.3, D26.3, D27.3, D28.3, D29.3, D30.3, D31.3, D32.3, D33.3, D34.3, D35.3, D36.3, D37.3, D38.3, D39.3, D40.3, D41.3, D42.3, D43.3, D44.3, D45.3, D46.3, D47.3, D48.3, D49.3, D50.3, D51.3, D52.3, D53.3, D54.3, D55.3, D56.3, D57.3, D58.3, D59.3, D60.3, D61.3, D62.3, D63.3, D64.3, D65.3, D66.3, D67.3, D68.3, D69.3, D70.3, D71.3, D72.3, D73.3, D74.3, D75.3, D76.3, D77.3, D78.3, D79.3, D80.3, D81.3, D82.3, D83.3, D84.3, D85.3, D86.3, D87.3, D88.3, D89.3, D90.3, D91.3, D92.3, D93.3, D94.3, D95.3, D96.3, D97.3, D98.3, D99.3, D100.3, D101.3, D102.3, D103.3, D104.3, D105.3, D106.3, D107.3, D108.3, D109.3, D110.3, D111.3, D112.3, D113.3, D114.3, D115.3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

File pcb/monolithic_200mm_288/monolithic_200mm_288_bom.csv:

Comment,Designator,Footprint,LCSC Part #
WS2812B-2020-V6,"D1 D2 D3 D4 D5 D6 D7 D8 D9 D10 D11 D12 D13 D14 D15 D16 D17 D18 D19 D20 D21 D22 D23 D24 D25 D26 D27 D28 D29 D30 D31 D32 D33 D34 D35 D36 D37 D38 D39 D40 D41 D42 D43 D44 D45 D46 D47 D48 D49 D50 D51 D52 D53 D54 D55 D56 D57 D58 D59 D60 D61 D62 D63 D64 D65 D66 D67 D68 D69 D70 D71 D72 D73 D74 D75 D76 D77 D78 D79 D80 D81 D82 D83 D84 D85 D86 D87 D88 D89 D90 D91 D92 D93 D94 D95 D96 D97 D98 D99 D100 D101 D102 D103 D104 D105 D106 D107 D108 D109 D110 D111 D112 D113 D114 D115 D116 D117 D118 D119 D120 D121 D122 D123 D124 D125 D126 D127 D128 D129 D130 D131 D132 D133 D134 D135 D136 D137 D138 D139 D140 D141 D142 D143 D144 D145 D146 D147 D148 D149 D150 D151 D152 D153 D154 D155 D156 D157 D158 D159 D160 D161 D162 D163 D164 D165 D166 D167 D168 D169 D170 D171 D172 D173 D174 D175 D176 D177 D178 D179 D180 D181 D182 D183 D184 D185 D186 D187 D188 D189 D190 D191 D192 D193 D194 D195 D196 D197 D198 D199 D200 D201 D202 D203 D204 D205 D206 D207 D208 D209 D210 D211 D212 D213 D214 D215 D216 D217 D218 D219 D220 D221 D222 D223 D224 D225 D226 D227 D228 D229 D230 D231 D232 D233 D234 D235 D236 D237 D238 D239 D240 D241 D242 D243 D244 D245 D246 D247 D248 D249 D250 D251 D252 D253 D254 D255 D256 D257 D258 D259 D260 D261 D262 D263 D264 D265 D266 D267 D268 D269 D270 D271 D272 D273 D274 D275 D276 D277 D278 D279 D280 D281 D282 D283 D284 D285 D286 D287 D288",LED_SMD:LED_WS2812B-2020_PLCC4_2.0x2.0mm,C52917434
100nF (0.1uF) 50V 0402,"C1 C2 C3 C4 C5 C6 C7 C8 C9 C10 C11 C12 C13 C14 C15 C16 C17 C18 C19 C20 C21 C22 C23 C24 C25 C26 C27 C28 C29 C30 C31 C32 C33 C34 C35 C36 C37 C38 C39 C40 C41 C42 C43 C44 C45 C46 C47 C48 C49 C50 C51 C52 C53 C54 C55 C56 C57 C58 C59 C60 C61 C62 C63 C64 C65 C66 C67 C68 C69 C70 C71 C72 C73 C74 C75 C76 C77 C78 C79 C80 C81 C82 C83 C84 C85 C86 C87 C88 C89 C90 C91 C92 C93 C94 C95 C96 C97 C98 C99 C100 C101 C102 C103 C104 C105 C106 C107 C108 C109 C110 C111 C112 C113 C114 C115 C116 C117 C118 C119 C120 C121 C122 C123 C124 C125 C126 C127 C128 C129 C130 C131 C132 C133 C134 C135 C136 C137 C138 C139 C140 C141 C142 C143 C144 C145 C146 C147 C148 C149 C150 C151 C152 C153 C154 C155 C156 C157 C158 C159 C160 C161 C162 C163 C164 C165 C166 C167 C168 C169 C170 C171 C172 C173 C174 C175 C176 C177 C178 C179 C180 C181 C182 C183 C184 C185 C186 C187 C188 C189 C190 C191 C192 C193 C194 C195 C196 C197 C198 C199 C200 C201 C202 C203 C204 C205 C206 C207 C208 C209 C210 C211 C212 C213 C214 C215 C216 C217 C218 C219 C220 C221 C222 C223 C224 C225 C226 C227 C228 C229 C230 C231 C232 C233 C234 C235 C236 C237 C238 C239 C240 C241 C242 C243 C244 C245 C246 C247 C248 C249 C250 C251 C252 C253 C254 C255 C256 C257 C258 C259 C260 C261 C262 C263 C264 C265 C266 C267 C268 C269 C270 C271 C272 C273 C274 C275 C276 C277 C278 C279 C280 C281 C282 C283 C284 C285 C286 C287 C288",Capacitor_SMD:C_0402_1005Metric,C1525

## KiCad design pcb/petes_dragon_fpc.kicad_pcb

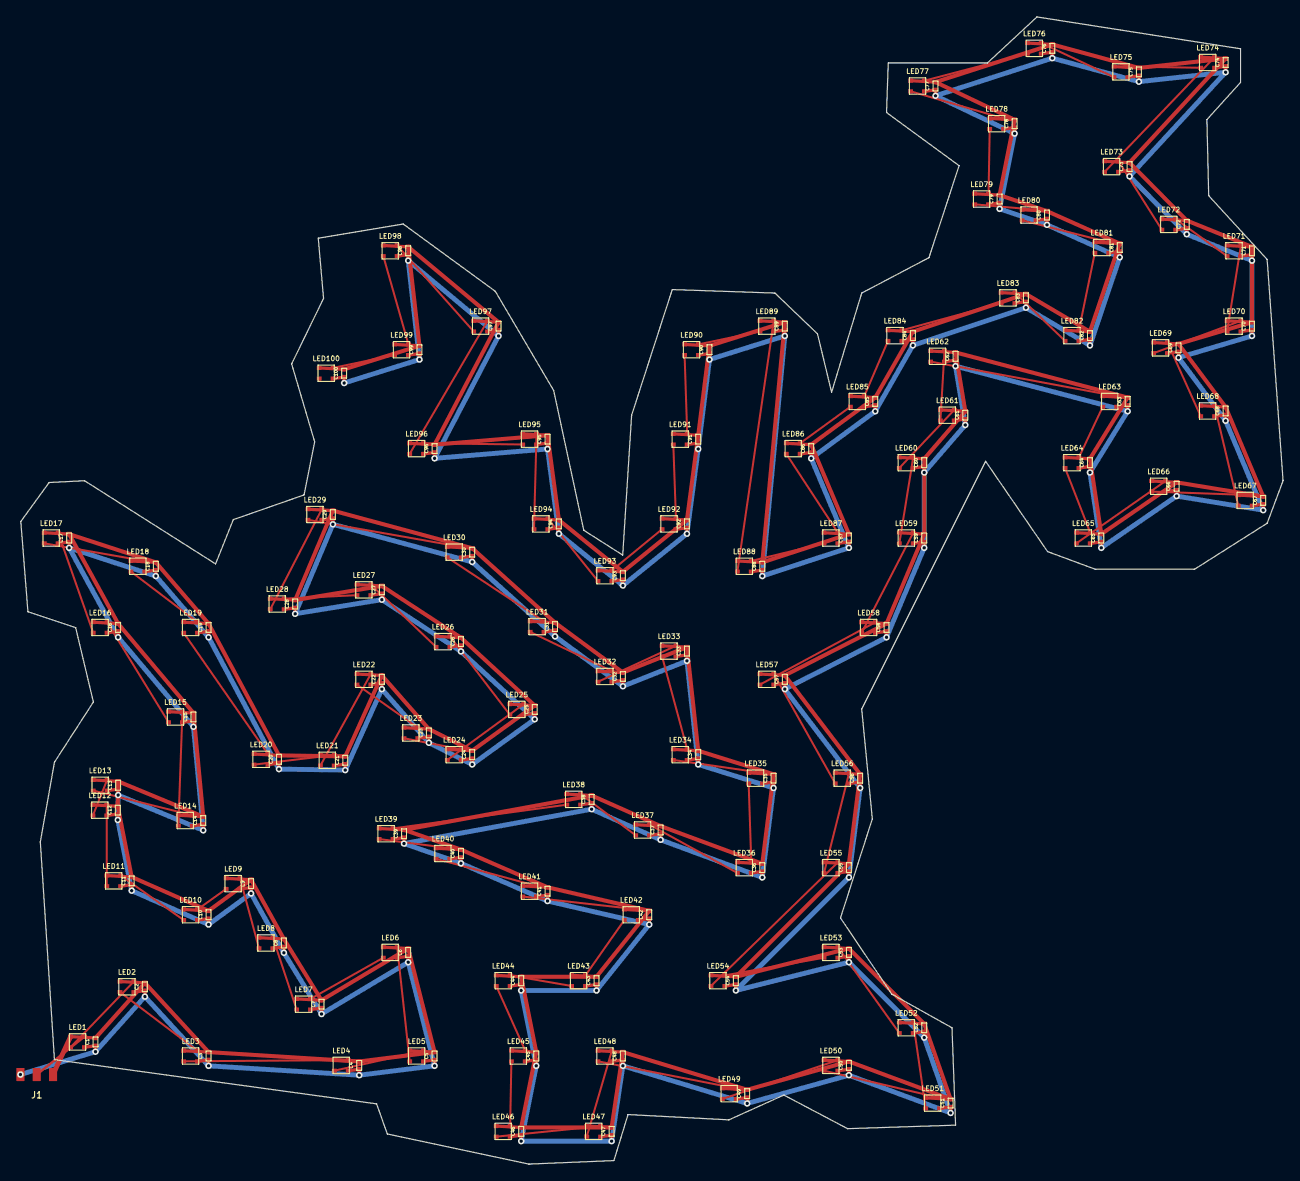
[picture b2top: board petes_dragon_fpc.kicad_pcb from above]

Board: 2 copper layers, 154.6 x 140.5 mm, 201 parts (0 on the bottom side), 102 nets.

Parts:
C1, C2, C3, C4, C5, C6, C7, C8, C9, C10, C11, C12, C13, C14, C15, C16, C17, C18, C19, C20, C21, C22, C23, C24, C25, C26, C27, C28, C29, C30, C31, C32, C33, C34, C35, C36, C37, C38, C39, C40, C41, C42, C43, C44, C45, C46, C47, C48, C49, C50, C51, C52, C53, C54, C55, C56, C57, C58, C59, C60, C61, C62, C63, C64, C65, C66, C67, C68, C69, C70, C71, C72, C73, C74, C75, C76, C77, C78, C79, C80, C81, C82, C83, C84, C85, C86, C87, C88, C89, C90, C91, C92, C93, C94, C95, C96, C97, C98, C99, C100: 100nF; C_0402_1005Metric
J1: JST-PH-3P; JST_PH_S3B-PH-SM4-TB_1x03-1MP_P2.00mm_Horizontal
LED1, LED2, LED3, LED4, LED5, LED6, LED7, LED8, LED9, LED10, LED11, LED12, LED13, LED14, LED15, LED16, LED17, LED18, LED19, LED20, LED21, LED22, LED23, LED24, LED25, LED26, LED27, LED28, LED29, LED30, LED31, LED32, LED33, LED34, LED35, LED36, LED37, LED38, LED39, LED40, LED41, LED42, LED43, LED44, LED45, LED46, LED47, LED48, LED49, LED50, LED51, LED52, LED53, LED54, LED55, LED56, LED57, LED58, LED59, LED60, LED61, LED62, LED63, LED64, LED65, LED66, LED67, LED68, LED69, LED70, LED71, LED72, LED73, LED74, LED75, LED76, LED77, LED78, LED79, LED80, LED81, LED82, LED83, LED84, LED85, LED86, LED87, LED88, LED89, LED90, LED91, LED92, LED93, LED94, LED95, LED96, LED97, LED98, LED99, LED100: WS2812B-2020; LED_WS2812B_PLCC4_2.0x2.0mm

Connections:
+5V: C1.1, C2.1, C3.1, C4.1, C5.1, C6.1, C7.1, C8.1, C9.1, C10.1, C11.1, C12.1, C13.1, C14.1, C15.1, C16.1, C17.1, C18.1, C19.1, C20.1, C21.1, C22.1, C23.1, C24.1, C25.1, C26.1, C27.1, C28.1, C29.1, C30.1, C31.1, C32.1, C33.1, C34.1, C35.1, C36.1, C37.1, C38.1, C39.1, C40.1, C41.1, C42.1, C43.1, C44.1, C45.1, C46.1, C47.1, C48.1, C49.1, C50.1, C51.1, C52.1, C53.1, C54.1, C55.1, C56.1, C57.1, C58.1, C59.1, C60.1, C61.1, C62.1, C63.1, C64.1, C65.1, C66.1, C67.1, C68.1, C69.1, C70.1, C71.1, C72.1, C73.1, C74.1, C75.1, C76.1, C77.1, C78.1, C79.1, C80.1, C81.1, C82.1, C83.1, C84.1, C85.1, C86.1, C87.1, C88.1, C89.1, C90.1, C91.1, C92.1, C93.1, C94.1, C95.1, C96.1, C97.1, C98.1, C99.1, C100.1, J1.1, LED1.1, LED2.1, LED3.1, LED4.1, LED5.1, LED6.1, LED7.1, LED8.1, LED9.1, LED10.1, LED11.1, LED12.1, LED13.1, LED14.1, LED15.1, LED16.1, LED17.1, LED18.1, LED19.1, LED20.1, LED21.1, LED22.1, LED23.1, LED24.1, LED25.1, LED26.1, LED27.1, LED28.1, LED29.1, LED30.1, LED31.1, LED32.1, LED33.1, LED34.1, LED35.1, LED36.1, LED37.1, LED38.1, LED39.1, LED40.1, LED41.1, LED42.1, LED43.1, LED44.1, LED45.1, LED46.1, LED47.1, LED48.1, LED49.1, LED50.1, LED51.1, LED52.1, LED53.1, LED54.1, LED55.1, LED56.1, LED57.1, LED58.1, LED59.1, LED60.1, LED61.1, LED62.1, LED63.1, LED64.1, LED65.1, LED66.1, LED67.1, LED68.1, LED69.1, LED70.1, LED71.1, LED72.1, LED73.1, LED74.1, LED75.1, LED76.1, LED77.1, LED78.1, LED79.1, LED80.1, LED81.1, LED82.1, LED83.1, LED84.1, LED85.1, LED86.1, LED87.1, LED88.1, LED89.1, LED90.1, LED91.1, LED92.1, LED93.1, LED94.1, LED95.1, LED96.1, LED97.1, LED98.1, LED99.1, LED100.1
DATA_1: J1.2, LED1.4
DATA_2: LED1.2, LED2.4
DATA_3: LED2.2, LED3.4
DATA_4: LED3.2, LED4.4
DATA_5: LED4.2, LED5.4
DATA_6: LED5.2, LED6.4
DATA_7: LED6.2, LED7.4
DATA_8: LED7.2, LED8.4
DATA_9: LED8.2, LED9.4
DATA_10: LED9.2, LED10.4
DATA_11: LED10.2, LED11.4
DATA_12: LED11.2, LED12.4
DATA_13: LED12.2, LED13.4
DATA_14: LED13.2, LED14.4
DATA_15: LED14.2, LED15.4
DATA_16: LED15.2, LED16.4
DATA_17: LED16.2, LED17.4
DATA_18: LED17.2, LED18.4
DATA_19: LED18.2, LED19.4
DATA_20: LED19.2, LED20.4
DATA_21: LED20.2, LED21.4
DATA_22: LED21.2, LED22.4
DATA_23: LED22.2, LED23.4
DATA_24: LED23.2, LED24.4
DATA_25: LED24.2, LED25.4
DATA_26: LED25.2, LED26.4
DATA_27: LED26.2, LED27.4
DATA_28: LED27.2, LED28.4
DATA_29: LED28.2, LED29.4
DATA_30: LED29.2, LED30.4
DATA_31: LED30.2, LED31.4
DATA_32: LED31.2, LED32.4
DATA_33: LED32.2, LED33.4
DATA_34: LED33.2, LED34.4
DATA_35: LED34.2, LED35.4
DATA_36: LED35.2, LED36.4
DATA_37: LED36.2, LED37.4
DATA_38: LED37.2, LED38.4
DATA_39: LED38.2, LED39.4
DATA_40: LED39.2, LED40.4
DATA_41: LED40.2, LED41.4
DATA_42: LED41.2, LED42.4
DATA_43: LED42.2, LED43.4
DATA_44: LED43.2, LED44.4
DATA_45: LED44.2, LED45.4
DATA_46: LED45.2, LED46.4
DATA_47: LED46.2, LED47.4
DATA_48: LED47.2, LED48.4
DATA_49: LED48.2, LED49.4
DATA_50: LED49.2, LED50.4
DATA_51: LED50.2, LED51.4
DATA_52: LED51.2, LED52.4
DATA_53: LED52.2, LED53.4
DATA_54: LED53.2, LED54.4
DATA_55: LED54.2, LED55.4
DATA_56: LED55.2, LED56.4
DATA_57: LED56.2, LED57.4
DATA_58: LED57.2, LED58.4
DATA_59: LED58.2, LED59.4
DATA_60: LED59.2, LED60.4
DATA_61: LED60.2, LED61.4
DATA_62: LED61.2, LED62.4
DATA_63: LED62.2, LED63.4
DATA_64: LED63.2, LED64.4
DATA_65: LED64.2, LED65.4
DATA_66: LED65.2, LED66.4
DATA_67: LED66.2, LED67.4
DATA_68: LED67.2, LED68.4
DATA_69: LED68.2, LED69.4
DATA_70: LED69.2, LED70.4
DATA_71: LED70.2, LED71.4
DATA_72: LED71.2, LED72.4
DATA_73: LED72.2, LED73.4
DATA_74: LED73.2, LED74.4
DATA_75: LED74.2, LED75.4
DATA_76: LED75.2, LED76.4
DATA_77: LED76.2, LED77.4
DATA_78: LED77.2, LED78.4
DATA_79: LED78.2, LED79.4
DATA_80: LED79.2, LED80.4
DATA_81: LED80.2, LED81.4
DATA_82: LED81.2, LED82.4
DATA_83: LED82.2, LED83.4
DATA_84: LED83.2, LED84.4
DATA_85: LED84.2, LED85.4
DATA_86: LED85.2, LED86.4
DATA_87: LED86.2, LED87.4
DATA_88: LED87.2, LED88.4
DATA_89: LED88.2, LED89.4
DATA_90: LED89.2, LED90.4
DATA_91: LED90.2, LED91.4
DATA_92: LED91.2, LED92.4
DATA_93: LED92.2, LED93.4
DATA_94: LED93.2, LED94.4
DATA_95: LED94.2, LED95.4
DATA_96: LED95.2, LED96.4
DATA_97: LED96.2, LED97.4
DATA_98: LED97.2, LED98.4
DATA_99: LED98.2, LED99.4
DATA_100: LED99.2, LED100.4
GND: C1.2, C2.2, C3.2, C4.2, C5.2, C6.2, C7.2, C8.2, C9.2, C10.2, C11.2, C12.2, C13.2, C14.2, C15.2, C16.2, C17.2, C18.2, C19.2, C20.2, C21.2, C22.2, C23.2, C24.2, C25.2, C26.2, C27.2, C28.2, C29.2, C30.2, C31.2, C32.2, C33.2, C34.2, C35.2, C36.2, C37.2, C38.2, C39.2, C40.2, C41.2, C42.2, C43.2, C44.2, C45.2, C46.2, C47.2, C48.2, C49.2, C50.2, C51.2, C52.2, C53.2, C54.2, C55.2, C56.2, C57.2, C58.2, C59.2, C60.2, C61.2, C62.2, C63.2, C64.2, C65.2, C66.2, C67.2, C68.2, C69.2, C70.2, C71.2, C72.2, C73.2, C74.2, C75.2, C76.2, C77.2, C78.2, C79.2, C80.2, C81.2, C82.2, C83.2, C84.2, C85.2, C86.2, C87.2, C88.2, C89.2, C90.2, C91.2, C92.2, C93.2, C94.2, C95.2, C96.2, C97.2, C98.2, C99.2, C100.2, J1.3, LED1.3, LED2.3, LED3.3, LED4.3, LED5.3, LED6.3, LED7.3, LED8.3, LED9.3, LED10.3, LED11.3, LED12.3, LED13.3, LED14.3, LED15.3, LED16.3, LED17.3, LED18.3, LED19.3, LED20.3, LED21.3, LED22.3, LED23.3, LED24.3, LED25.3, LED26.3, LED27.3, LED28.3, LED29.3, LED30.3, LED31.3, LED32.3, LED33.3, LED34.3, LED35.3, LED36.3, LED37.3, LED38.3, LED39.3, LED40.3, LED41.3, LED42.3, LED43.3, LED44.3, LED45.3, LED46.3, LED47.3, LED48.3, LED49.3, LED50.3, LED51.3, LED52.3, LED53.3, LED54.3, LED55.3, LED56.3, LED57.3, LED58.3, LED59.3, LED60.3, LED61.3, LED62.3, LED63.3, LED64.3, LED65.3, LED66.3, LED67.3, LED68.3, LED69.3, LED70.3, LED71.3, LED72.3, LED73.3, LED74.3, LED75.3, LED76.3, LED77.3, LED78.3, LED79.3, LED80.3, LED81.3, LED82.3, LED83.3, LED84.3, LED85.3, LED86.3, LED87.3, LED88.3, LED89.3, LED90.3, LED91.3, LED92.3, LED93.3, LED94.3, LED95.3, LED96.3, LED97.3, LED98.3, LED99.3, LED100.3

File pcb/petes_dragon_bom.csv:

Comment,Designator,Footprint,LCSC Part #
"WS2812B-2020 Addressable RGB LED","LED1 LED2 LED3 LED4 LED5 LED6 LED7 LED8 LED9 LED10 LED11 LED12 LED13 LED14 LED15 LED16 LED17 LED18 LED19 LED20 LED21 LED22 LED23 LED24 LED25 LED26 LED27 LED28 LED29 LED30 LED31 LED32 LED33 LED34 LED35 LED36 LED37 LED38 LED39 LED40 LED41 LED42 LED43 LED44 LED45 LED46 LED47 LED48 LED49 LED50 LED51 LED52 LED53 LED54 LED55 LED56 LED57 LED58 LED59 LED60 LED61 LED62 LED63 LED64 LED65 LED66 LED67 LED68 LED69 LED70 LED71 LED72 LED73 LED74 LED75 LED76 LED77 LED78 LED79 LED80 LED81 LED82 LED83 LED84 LED85 LED86 LED87 LED88 LED89 LED90 LED91 LED92 LED93 LED94 LED95 LED96 LED97 LED98 LED99 LED100","LED-SMD_4P-L2.0-W2.0-TL","C2843818"
"100nF (0.1uF) 50V 0402 Capacitor","C1 C2 C3 C4 C5 C6 C7 C8 C9 C10 C11 C12 C13 C14 C15 C16 C17 C18 C19 C20 C21 C22 C23 C24 C25 C26 C27 C28 C29 C30 C31 C32 C33 C34 C35 C36 C37 C38 C39 C40 C41 C42 C43 C44 C45 C46 C47 C48 C49 C50 C51 C52 C53 C54 C55 C56 C57 C58 C59 C60 C61 C62 C63 C64 C65 C66 C67 C68 C69 C70 C71 C72 C73 C74 C75 C76 C77 C78 C79 C80 C81 C82 C83 C84 C85 C86 C87 C88 C89 C90 C91 C92 C93 C94 C95 C96 C97 C98 C99 C100","C0402","C1525"
"JST-PH-3P SMT 2.0mm Header","J1","JST_PH_S3B-PH-SM4-TB","C145946"
